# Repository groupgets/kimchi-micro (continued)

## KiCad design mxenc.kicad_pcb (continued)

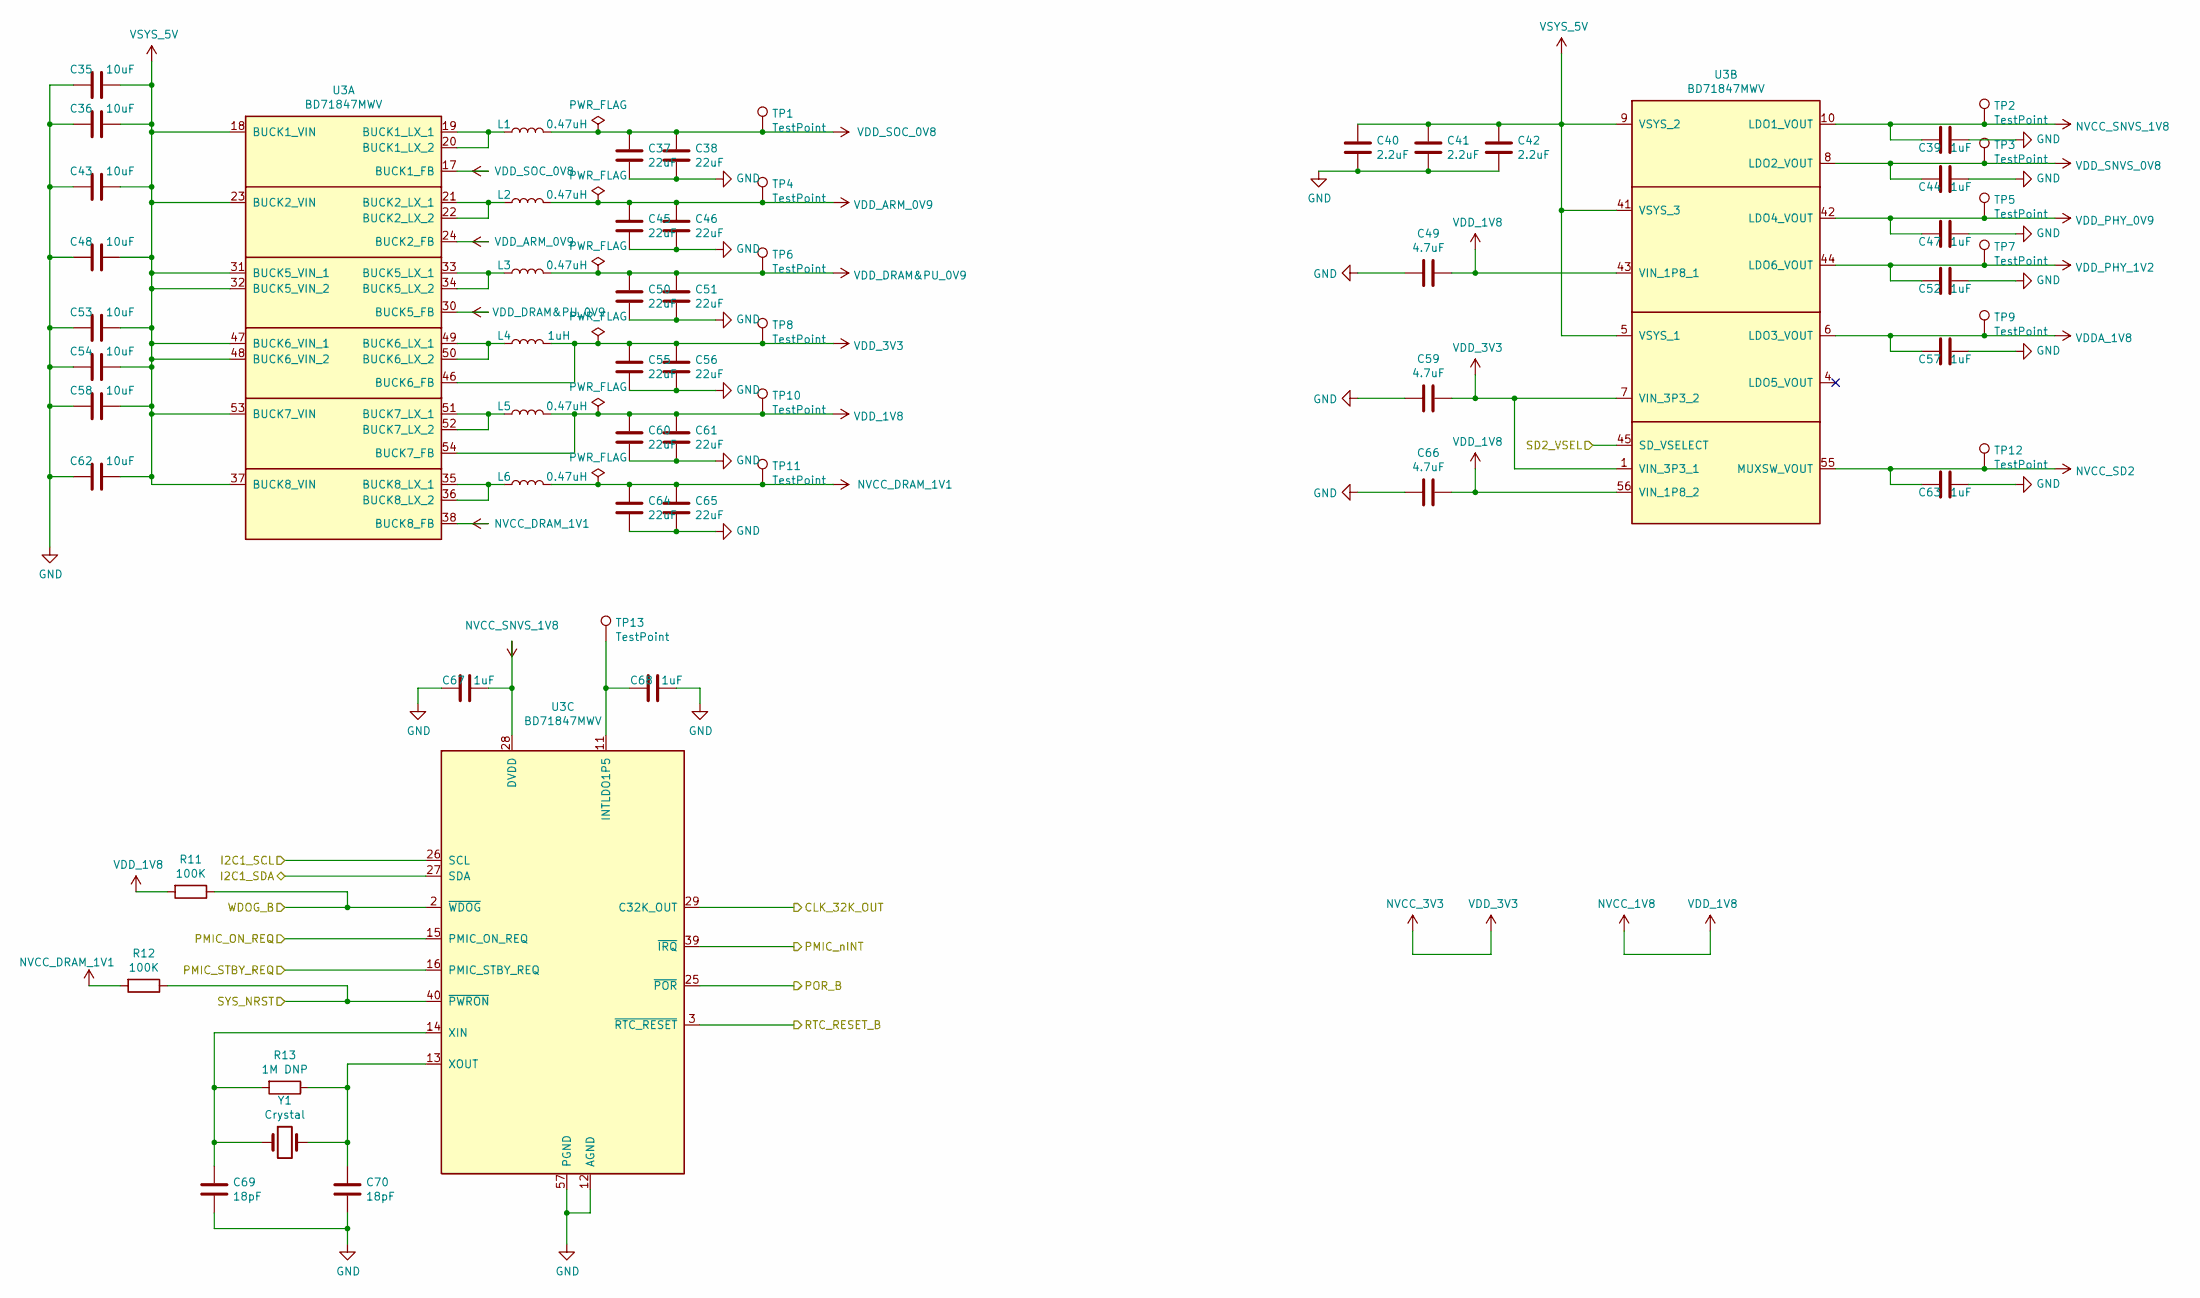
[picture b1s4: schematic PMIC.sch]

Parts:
C35, C36, C43, C48, C53, C54, C58, C62: 10uF; C_0603_1608Metric; Part CL10X106MO8NRNC
C37, C38, C45, C46, C50, C51, C55, C56, C60, C61, C64, C65: 22uF; C_0603_1608Metric; Part GRM188C80G226MEA0D
C39, C44, C47, C52, C57, C67, C68: 1uF; C_0402_1005Metric; Part GRM155C81A105KA12D
C40, C41, C42: 2.2uF; C_0402_1005Metric; Part GRM155C80J225ME95D
C49, C59, C66: 4.7uF; C_0402_1005Metric; Part GRM155C80J475MEAAD
C63: 1uF; C_0603_1608Metric; Part CL10B105MO8NNWC
C69, C70: 18pF; C_0402_1005Metric; Part GRM0335C1H180JA01D
L1, L2, L3, L5, L6: 0.47uH; L_0806; Part CIGT201610EHR47MNE
L4: 1uH; L_0806; Part CIGT201610EH1R0MNE
R11, R12: 100K; R_0402_1005Metric; Part RC0402JR-07100KL
R13: 1M DNP; R_0402_1005Metric
TP1, TP2, TP3, TP4, TP5, TP6, TP7, TP8, TP9, TP10, TP11, TP12, TP13: TestPoint; TestPoint_Pad_D1.0mm
U3: BD71847MWV; QFN-56_EP_7x7_Pitch0.4mm; Part BD71847AMWV-E2
Y1: Crystal; Crystal_SMD_3215-2Pin_3.2x1.5mm; Part ABS07-32.768KHZ-T

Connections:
/CLK_32K: U3.29 (C32K_OUT); also elsewhere on the board
/I2C1_SCL: U3.26 (SCL); also elsewhere on the board
/I2C1_SDA: U3.27 (SDA); also elsewhere on the board
/PMIC_ON_REQ: U3.15 (PMIC_ON_REQ); also elsewhere on the board
/PMIC_STBY_REQ: U3.16 (PMIC_STBY_REQ); also elsewhere on the board
/PMIC_nINT: U3.39 (~IRQ); also elsewhere on the board
/POR_B: U3.25 (~POR); also elsewhere on the board
/RTC_RESET_B: U3.3 (~RTC_RESET); also elsewhere on the board
/SD2_VSEL: U3.45 (SD_VSELECT); also elsewhere on the board
/SYS_NRST: R12.1, U3.40 (~PWRON)
/WDOG_B: R11.1, U3.2 (~WDOG); also elsewhere on the board
GND: C35.2, C36.2, C37.1, C38.1, C39.1, C40.2, C41.2, C42.2, C43.2, C44.1, C45.1, C46.1, C47.1, C48.2, C49.1, C50.1, C51.1, C52.1, C53.2, C54.2, C55.1, C56.1, C57.1, C58.2, C59.1, C60.1, C61.1, C62.2, C63.1, C64.1, C65.1, C66.1, C67.1, C68.2, C69.1, C70.1, U3.12 (AGND), U3.57 (PGND); also elsewhere on the board
NVCC_1V8: C49.2, C60.2, C61.2, C66.2, L5.2, R11.2, TP10.1, U3.43 (VIN_1P8_1), U3.54 (BUCK7_FB), U3.56 (VIN_1P8_2); also elsewhere on the board
NVCC_3V3: C55.2, C56.2, C59.2, L4.2, TP8.1, U3.1 (VIN_3P3_1), U3.7 (VIN_3P3_2), U3.46 (BUCK6_FB); also elsewhere on the board
NVCC_DRAM_1V1: C64.2, C65.2, L6.2, R12.2, TP11.1, U3.38 (BUCK8_FB); also elsewhere on the board
NVCC_SD2: C63.2, TP12.1, U3.55 (MUXSW_VOUT); also elsewhere on the board
NVCC_SNVS_1V8: C39.2, C67.2, TP2.1, U3.10 (LDO1_VOUT), U3.28 (DVDD); also elsewhere on the board
unnamed: C68.1, TP13.1, U3.11 (INTLDO1P5)
unnamed: C69.2, R13.2, U3.14 (XIN), Y1.1
unnamed: C70.2, R13.1, U3.13 (XOUT), Y1.2
unnamed: L1.1, U3.19 (BUCK1_LX_1), U3.20 (BUCK1_LX_2)
unnamed: L2.1, U3.21 (BUCK2_LX_1), U3.22 (BUCK2_LX_2)
unnamed: L3.1, U3.33 (BUCK5_LX_1), U3.34 (BUCK5_LX_2)
unnamed: L4.1, U3.49 (BUCK6_LX_1), U3.50 (BUCK6_LX_2)
unnamed: L5.1, U3.51 (BUCK7_LX_1), U3.52 (BUCK7_LX_2)
unnamed: L6.1, U3.35 (BUCK8_LX_1), U3.36 (BUCK8_LX_2)
VDDA_1V8: C57.2, TP9.1, U3.6 (LDO3_VOUT); also elsewhere on the board
VDD_ARM_0V9: C45.2, C46.2, L2.2, TP4.1, U3.24 (BUCK2_FB); also elsewhere on the board
VDD_DRAM&PU_0V9: C50.2, C51.2, L3.2, TP6.1, U3.30 (BUCK5_FB); also elsewhere on the board
VDD_PHY_0V9: C47.2, TP5.1, U3.42 (LDO4_VOUT); also elsewhere on the board
VDD_PHY_1V2: C52.2, TP7.1, U3.44 (LDO6_VOUT); also elsewhere on the board
VDD_SNVS_0V8: C44.2, TP3.1, U3.8 (LDO2_VOUT); also elsewhere on the board
VDD_SOC_0V8: C37.2, C38.2, L1.2, TP1.1, U3.17 (BUCK1_FB); also elsewhere on the board
VSYS_5V: C35.1, C36.1, C40.1, C41.1, C42.1, C43.1, C48.1, C53.1, C54.1, C58.1, C62.1, U3.5 (VSYS_1), U3.9 (VSYS_2), U3.18 (BUCK1_VIN), U3.23 (BUCK2_VIN), U3.31 (BUCK5_VIN_1), U3.32 (BUCK5_VIN_2), U3.37 (BUCK8_VIN), U3.41 (VSYS_3), U3.47 (BUCK6_VIN_1), U3.48 (BUCK6_VIN_2), U3.53 (BUCK7_VIN); also elsewhere on the board

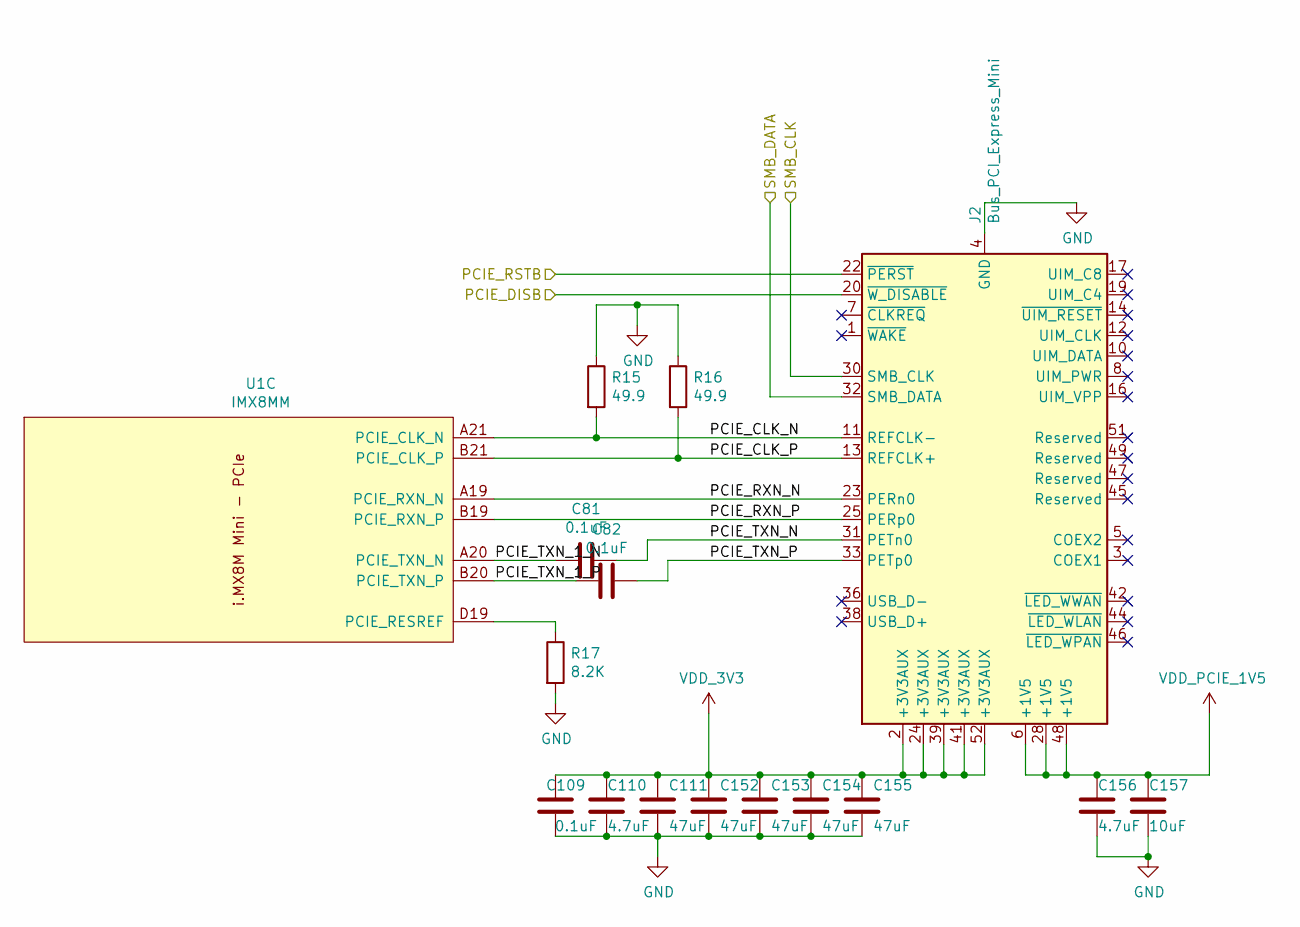
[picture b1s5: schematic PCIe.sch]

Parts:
C81, C82, C109: 0.1uF; C_0201_0603Metric; Part GRM033C80J104KE15D
C110, C156: 4.7uF; C_0402_1005Metric; Part GRM155C80J475MEAAD
C111, C152, C153, C154, C155: 47uF; C_0805_2012Metric; Part GRM21BC80G476ME15L
C157: 10uF; C_0402_1005Metric; Part GRM155C80J106ME11D
J2: Bus_PCI_Express_Mini; 1775838-2-NPTH; Part 1775838-2
R15, R16: 49.9; R_0201_0603Metric; Part RC0201FR-0749R9L
R17: 8.2K; R_0201_0603Metric; Part RC0201FR-078K2L
U1: IMX8MM; BGA-729_27x27_14.0x14.0mm; Part MIMX8MM6CVTKZAA

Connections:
/I2C3_SCL: J2.30 (SMB_CLK); also elsewhere on the board
/I2C3_SDA: J2.32 (SMB_DATA); also elsewhere on the board
/PCIE_DISB: J2.20 (~W_DISABLE); also elsewhere on the board
/PCIE_RSTB: J2.22 (~PERST); also elsewhere on the board
/PCIe/PCIE_CLK_N: J2.11 (REFCLK-), R15.2, U1.A21 (PCIE_CLK_N)
/PCIe/PCIE_CLK_P: J2.13 (REFCLK+), R16.2, U1.B21 (PCIE_CLK_P)
/PCIe/PCIE_RXN_N: J2.23 (PERn0), U1.A19 (PCIE_RXN_N)
/PCIe/PCIE_RXN_P: J2.25 (PERp0), U1.B19 (PCIE_RXN_P)
/PCIe/PCIE_TXN_1_N: C81.2, U1.A20 (PCIE_TXN_N)
/PCIe/PCIE_TXN_1_P: C82.2, U1.B20 (PCIE_TXN_P)
/PCIe/PCIE_TXN_N: C81.1, J2.31 (PETn0)
/PCIe/PCIE_TXN_P: C82.1, J2.33 (PETp0)
GND: C109.2, C110.2, C111.2, C152.2, C153.2, C154.2, C155.2, C156.2, C157.2, J2.4 (GND), J2.9 (GND), J2.15 (GND), J2.18 (GND), J2.21 (GND), J2.26 (GND), J2.27 (GND), J2.29 (GND), J2.34 (GND), J2.35 (GND), J2.37 (GND), J2.40 (GND), J2.43 (GND), J2.50 (GND), R15.1, R16.1, R17.2; also elsewhere on the board
NVCC_3V3: C109.1, C110.1, C111.1, C152.1, C153.1, C154.1, C155.1, J2.2 (+3V3AUX), J2.24 (+3V3AUX), J2.39 (+3V3AUX), J2.41 (+3V3AUX), J2.52 (+3V3AUX); also elsewhere on the board
unnamed: R17.1, U1.D19 (PCIE_RESREF)
VDD_PCIE_1V5: C156.1, C157.1, J2.6 (+1V5), J2.28 (+1V5), J2.48 (+1V5); also elsewhere on the board

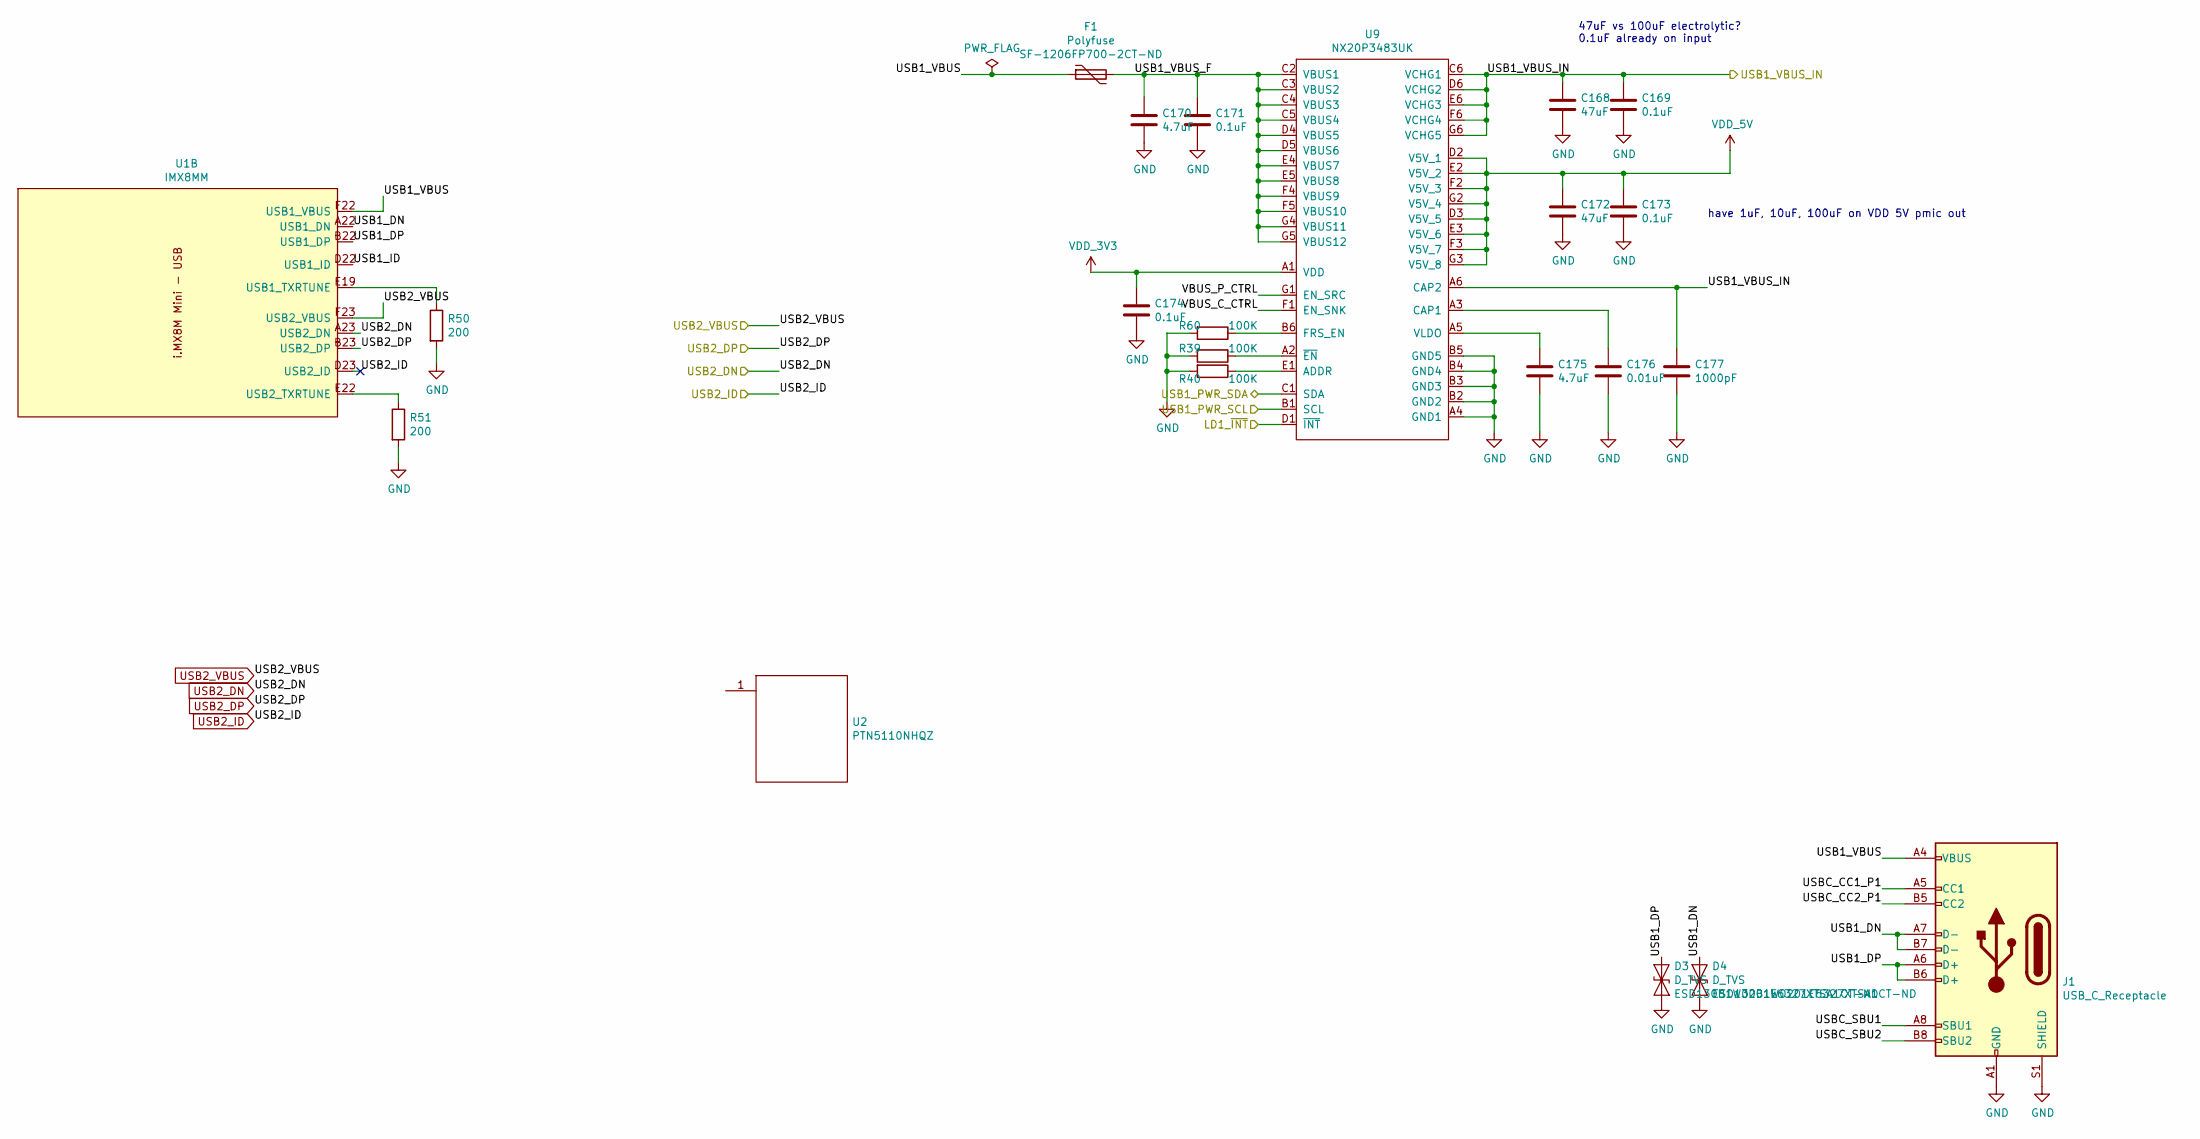
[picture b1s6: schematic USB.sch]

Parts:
C168, C172: 47uF; C_1210_3225Metric; Part GRM32EC81C476ME15L
C169, C171, C173, C174: 0.1uF; C_0402_1005Metric; Part GRM155R71E104KE14J
C170: 4.7uF; C_1210_3225Metric; Part CC1210MKX7R6BB475
C175: 4.7uF; C_0603_1608Metric; Part JMK107C6475MA-T
C176: 0.01uF; C_0201_0603Metric; Part GRM033R71C103KE14D
C177: 1000pF; C_0201_0603Metric; Part GRM033R71H102KA12J
D3, D4: D_TVS; D_0201_0603Metric; Part ESD130B1W0201E6327XTSA1
F1: Polyfuse; C_1206_3216Metric; Part SF-1206FP700-2
J1: USB_C_Receptacle; GCT_USB4110-GF-A; Part DX07S024JJ2R1300
R39, R40, R60: 100K; R_0201_0603Metric; Part RC0201JR-07100KL
R50, R51: 200; R_0201_0603Metric; Part RC0201FR-07200RL
U1: IMX8MM; BGA-729_27x27_14.0x14.0mm; Part MIMX8MM6CVTKZAA
U2: PTN5110NHQZ; HX2QFN-16_EP_2.85x2.85_Pitch0.4mm
U9: NX20P3483UK; BGA-42_6x7_2.51x2.91mm; Part NX20P3483UK

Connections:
/I2C3_SCL: U9.B1 (SCL); also elsewhere on the board
/I2C3_SDA: U9.C1 (SDA); also elsewhere on the board
/LD1_~INT: U9.D1 (~INT); also elsewhere on the board
/USB/USB1_DN: D4.1 (A1), J1.A7 (D-), J1.B7 (D-), U1.A22 (USB1_DN)
/USB/USB1_DP: D3.1 (A1), J1.A6 (D+), J1.B6 (D+), U1.B22 (USB1_DP)
/USB/USB1_VBUS: F1.1, J1.A4 (VBUS), J1.A9 (VBUS), J1.B4 (VBUS), J1.B9 (VBUS), U1.F22 (USB1_VBUS)
/USB/USB1_VBUS_F: C170.1, C171.1, F1.2, U9.C2 (VBUS1), U9.C3 (VBUS2), U9.C4 (VBUS3), U9.C5 (VBUS4), U9.D4 (VBUS5), U9.D5 (VBUS6), U9.E4 (VBUS7), U9.E5 (VBUS8), U9.F4 (VBUS9), U9.F5 (VBUS10), U9.G4 (VBUS11), U9.G5 (VBUS12)
/VBUS_IN: C168.1, C169.1, C177.1, U9.A6 (CAP2), U9.C6 (VCHG1), U9.D6 (VCHG2), U9.E6 (VCHG3), U9.F6 (VCHG4), U9.G6 (VCHG5); also elsewhere on the board
GND: C168.2, C169.2, C170.2, C171.2, C172.2, C173.2, C174.2, C175.2, C176.2, C177.2, D3.2 (A2), D4.2 (A2), J1.A1 (GND), J1.A12 (GND), J1.B1 (GND), J1.B12 (GND), J1.S1 (SHIELD), R39.2, R40.2, R50.2, R51.2, R60.2, U9.A4 (GND1), U9.B2 (GND2), U9.B3 (GND3), U9.B4 (GND4), U9.B5 (GND5); also elsewhere on the board
NVCC_3V3: C174.1, U9.A1 (VDD); also elsewhere on the board
unnamed: C175.1, U9.A5 (VLDO)
unnamed: C176.1, U9.A3 (CAP1)
unnamed: R39.1, U9.A2 (~EN)
unnamed: R40.1, U9.E1 (ADDR)
unnamed: R50.1, U1.E19 (USB1_TXRTUNE)
unnamed: R51.1, U1.E22 (USB2_TXRTUNE)
unnamed: R60.1, U9.B6 (FRS_EN)
USB2_DN: U1.A23 (USB2_DN); also elsewhere on the board
USB2_DP: U1.B23 (USB2_DP); also elsewhere on the board
USB2_ID: U1.D23 (USB2_ID); also elsewhere on the board
USB2_VBUS: U1.F23 (USB2_VBUS); also elsewhere on the board
VDD_5V: C172.1, C173.1, U9.D2 (V5V_1), U9.D3 (V5V_5), U9.E2 (V5V_2), U9.E3 (V5V_6), U9.F2 (V5V_3), U9.F3 (V5V_7), U9.G2 (V5V_4), U9.G3 (V5V_8); also elsewhere on the board

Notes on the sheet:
47uF vs 100uF electrolytic? 0.1uF already on input
have 1uF, 10uF, 100uF on VDD 5V pmic out

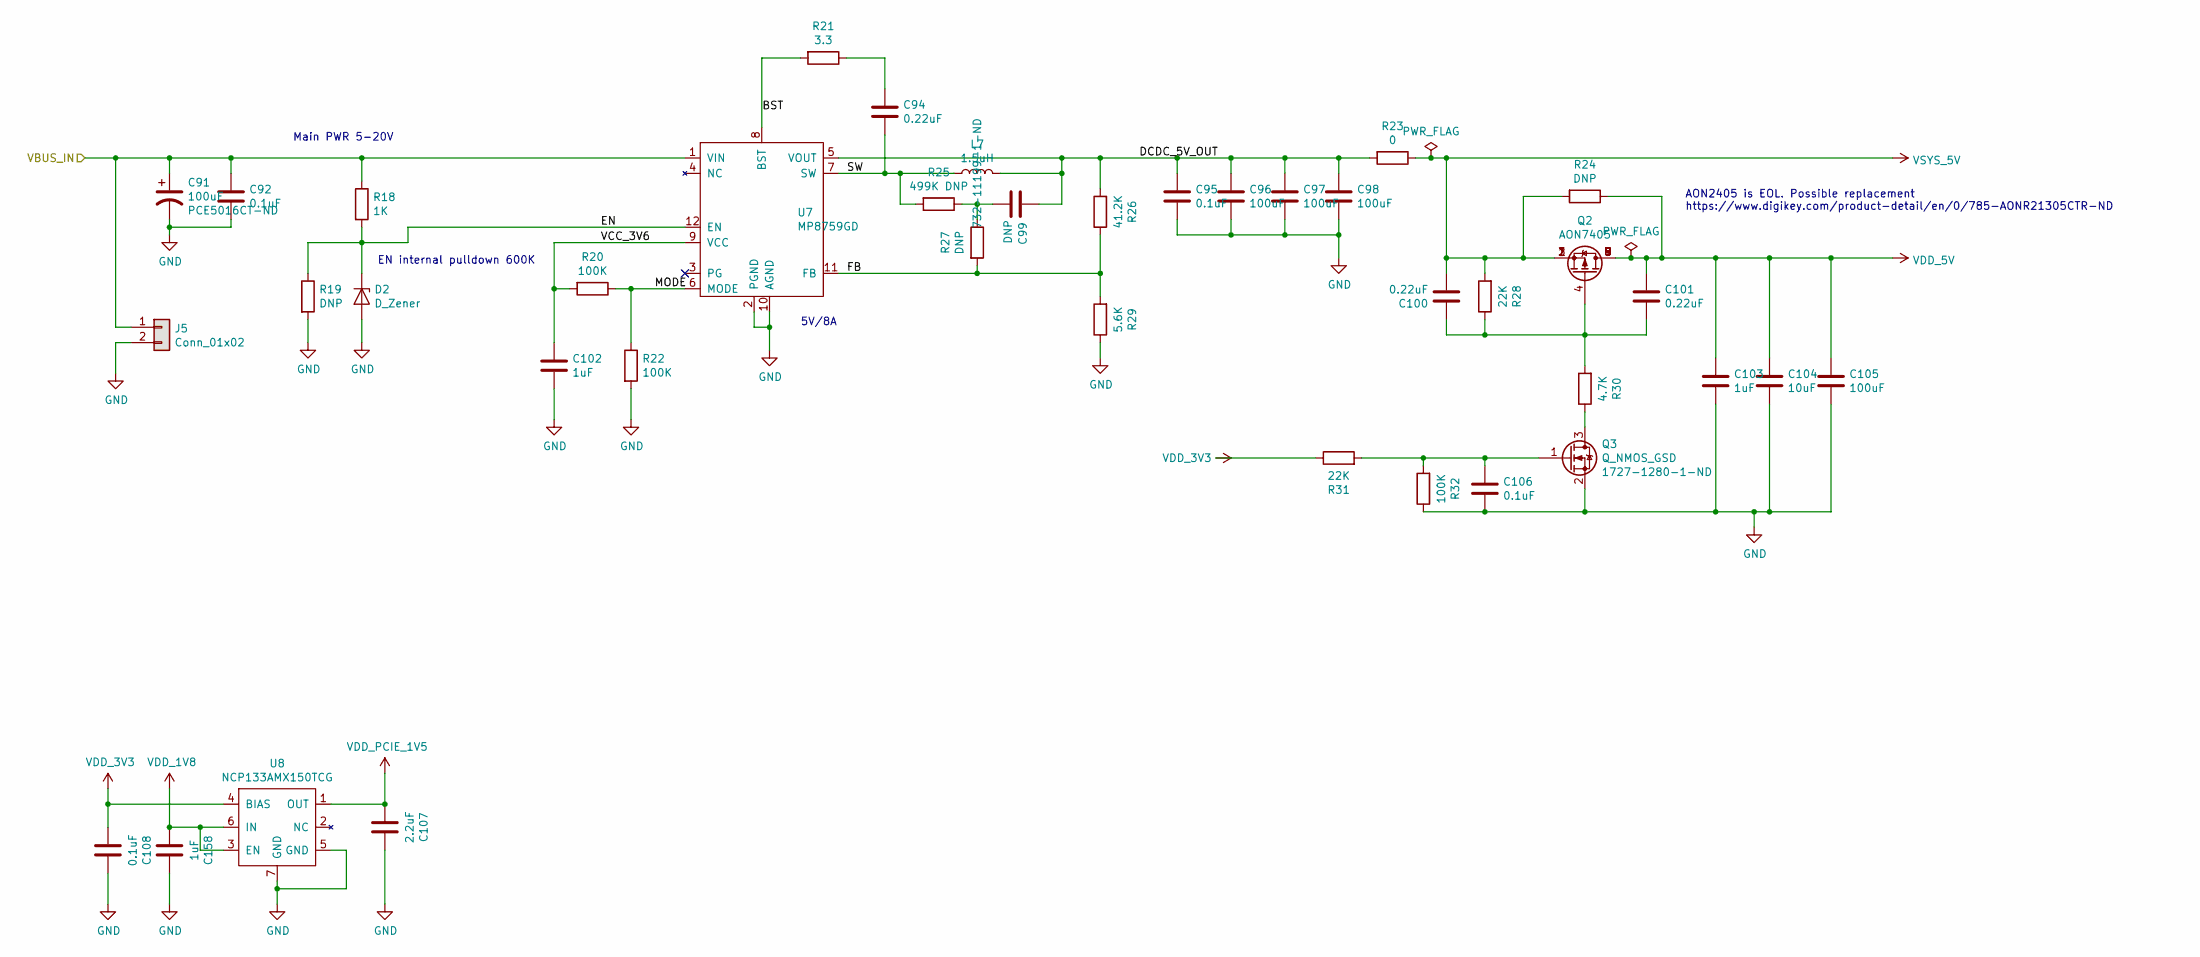
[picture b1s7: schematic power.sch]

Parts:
C91: 100uF; C_Elec_6.3x5.8; Part EEE-FT1V101AP
C92, C95, C106: 0.1uF; C_0402_1005Metric; Part GRM155R71E104KE14J
C94, C100, C101: 0.22uF; C_0402_1005Metric; Part GRM155C8YA224ME01D
C96, C97, C98, C105: 100uF; C_1210_3225Metric; Part GRM32EC70J107ME15L
C99: DNP; C_0402_1005Metric
C102, C103, C158: 1uF; C_0402_1005Metric; Part GRM155C81A105KA12D
C104: 10uF; C_0805_2012Metric_Pad1.15x1.40mm_HandSolder; Part CL21X106KPYNNNE
C107: 2.2uF; C_0402_1005Metric; Part GRM155C80J225ME95D
C108: 0.1uF; C_0201_0603Metric; Part GRM033C80J104KE15D
D2: D_Zener; D_SOD-323; Part MM3Z4V3ST1G
J5: Conn_01x02; JST_XH_B2B-XH-A_1x02_P2.50mm_Vertical; Part SM02B-GHS-TB(LF)(SN)
L7: 1.5uH; L_Wuerth_MAPI-4020; Part 74438357015
Q2: AON7405; DFN-8-1EP_3x3mm_P0.65mm_EP1.7x2.05mm; Part AON7405
Q3: Q_NMOS_GSD; SOT-323_SC-70; Part NX3008NBKW,115
R18: 1K; R_0402_1005Metric; Part RC0402JR-071KL
R19, R24, R27: DNP; R_0402_1005Metric
R20, R22, R32: 100K; R_0402_1005Metric; Part RC0402JR-07100KL
R21: 3.3; R_0603_1608Metric; Part MCT06030C3308FP500
R23: 0; R_0805_2012Metric; Part CRCW08050000Z0EAHP
R25: 499K DNP; R_0402_1005Metric
R26: 41.2K; R_0402_1005Metric; Part ERJ-2RKF4122X
R28, R31: 22K; R_0402_1005Metric; Part ERJ-2GEJ223X
R29: 5.6K; R_0402_1005Metric; Part ERJ-2RKF5601X
R30: 4.7K; R_0402_1005Metric; Part ERJ-2RKF4701X
U7: MP8759GD; QFN-16_2x3_Pitch0.5mm; Part MP8759GD-Z
U8: NCP133AMX150TCG; XDFN6_1.20x1.20_0.40P; Part NCP133AMX150TCG

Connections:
/Power/BST: R21.2, U7.8 (BST)
/Power/DCDC_5V_OUT: C95.1, C96.1, C97.1, C98.1, C99.1, L7.2, R23.2, R26.2, U7.5 (VOUT)
/Power/EN: D2.1 (K), R18.2, R19.1, U7.12 (EN)
/Power/FB: R26.1, R27.2, R29.2, U7.11 (FB)
/Power/MODE: R20.1, R22.1, U7.6 (MODE)
/Power/SW: C94.2, L7.1, R25.2, U7.7 (SW)
/Power/VCC_3V6: C102.1, R20.2, U7.9 (VCC)
/VBUS_IN: C91.1, C92.1, J5.1, R18.1, U7.1 (VIN); also elsewhere on the board
GND: C91.2, C92.2, C95.2, C96.2, C97.2, C98.2, C102.2, C103.2, C104.2, C105.2, C106.2, C107.1, C108.1, C158.1, D2.2 (A), J5.2, Q3.2 (S), R19.2, R22.2, R29.1, R32.1, U7.2 (PGND), U7.10 (AGND), U8.5 (GND), U8.7 (GND); also elsewhere on the board
NVCC_1V8: C158.2, U8.3 (EN), U8.6 (IN); also elsewhere on the board
NVCC_3V3: C108.2, R31.1, U8.4 (BIAS); also elsewhere on the board
unnamed: C94.1, R21.1
unnamed: C99.2, R25.1, R27.1
unnamed: C100.1, C101.2, Q2.4 (G), R28.1, R30.2
unnamed: C106.1, Q3.1 (G), R31.2, R32.2
unnamed: Q3.3 (D), R30.1
VDD_5V: C101.1, C103.1, C104.1, C105.1, Q2.5 (D), Q2.6 (D), Q2.7 (D), Q2.8 (D), Q2.9 (D), R24.1; also elsewhere on the board
VDD_PCIE_1V5: C107.2, U8.1 (OUT); also elsewhere on the board
VSYS_5V: C100.2, Q2.1 (S), Q2.2 (S), Q2.3 (S), R23.1, R24.2, R28.2; also elsewhere on the board

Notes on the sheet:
5V/8A
Main PWR 5-20V
EN internal pulldown 600K
AON2405 is EOL. Possible replacement https://www.digikey.com/product-detail/en/0/785-AONR21305CTR-ND

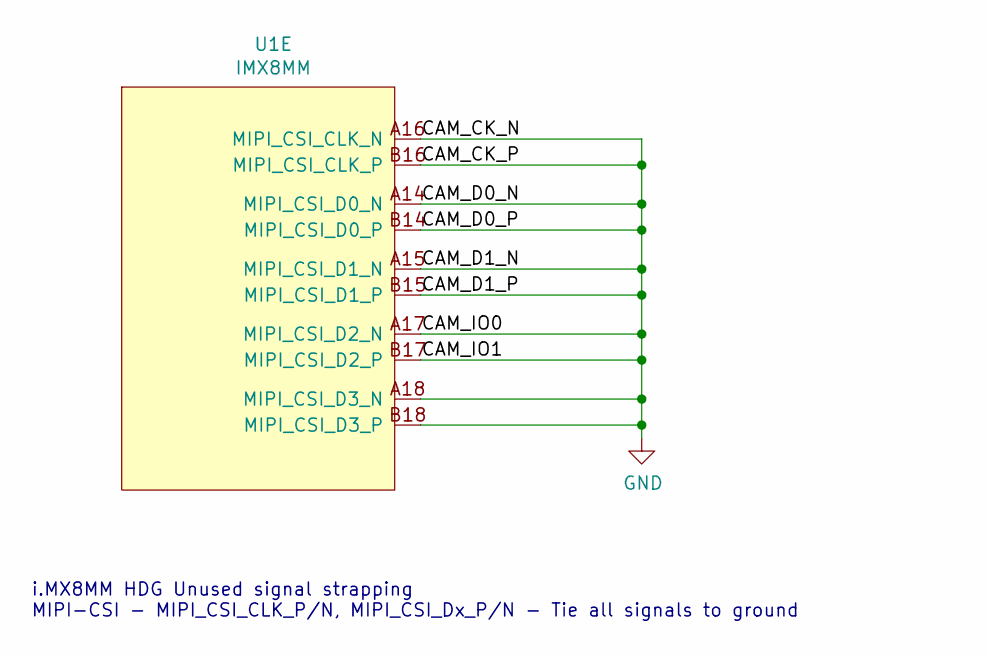
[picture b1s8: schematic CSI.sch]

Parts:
U1: IMX8MM; BGA-729_27x27_14.0x14.0mm; Part MIMX8MM6CVTKZAA

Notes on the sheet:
i.MX8MM HDG Unused signal strapping MIPI-CSI - MIPI_CSI_CLK_P/N, MIPI_CSI_Dx_P/N - Tie all signals to ground

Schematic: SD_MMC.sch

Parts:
C71: 4.7uF; C_0402_1005Metric; Part GRM155C80J475MEAAD
C72, C73, C74, C75, C76, C80: 0.22uF; C_0201_0603Metric; Part GRM033C80J224KE90D
C77: 10uF; C_0402_1005Metric; Part GRM155C80J106ME11D
C78: 0.22uF; C_0402_1005Metric; Part GRM155C8YA224ME01D
C79: 1uF; C_0402_1005Metric; Part GRM155C81A105KA12D
J3: Micro_SD_Card; 114-00841-68; Part 114-00841-68
R14: 10K; R_0402_1005Metric; Part ERJ-2GEJ103X
U1: IMX8MM; BGA-729_27x27_14.0x14.0mm; Part MIMX8MM6CVTKZAA
U5: SDINBDG4-8G; BGA153C50P14X14_1300X1150X80N; Part SDINBDG4-8G-I1

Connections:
/SD/MMC/EMMC_CLK: U1.V26 (SD1_CLK), U5.M6 (CLK)
/SD/MMC/EMMC_CMD: U1.V27 (SD1_CMD), U5.M5 (CMD)
/SD/MMC/EMMC_DAT0: U1.Y27 (SD1_DATA0), U5.A3 (DAT0)
/SD/MMC/EMMC_DAT1: U1.Y26 (SD1_DATA1), U5.A4 (DAT1)
/SD/MMC/EMMC_DAT2: U1.T27 (SD1_DATA2), U5.A5 (DAT2)
/SD/MMC/EMMC_DAT3: U1.T26 (SD1_DATA3), U5.B2 (DAT3)
/SD/MMC/EMMC_DAT4: U1.U27 (SD1_DATA4), U5.B3 (DAT4)
/SD/MMC/EMMC_DAT5: U1.U26 (SD1_DATA5), U5.B4 (DAT5)
/SD/MMC/EMMC_DAT6: U1.W27 (SD1_DATA6), U5.B5 (DAT6)
/SD/MMC/EMMC_DAT7: U1.W26 (SD1_DATA7), U5.B6 (DAT7)
/SD/MMC/EMMC_RCLK: U1.R24 (SD1_STROBE), U5.H5 (RCLK)
/SD/MMC/EMMC_RST: U1.R23 (NAND_DQS/GPIO3[14]), U5.K5 (RST_N)
/SD/MMC/EMMC_VDDI: C79.1, C80.1, U5.C2 (VDDI)
/SD/MMC/SD_CD: J3.10 (DET_A), R14.1, U1.AA26 (SD2_CD_B)
/SD/MMC/SD_CLK: J3.5 (CLK), U1.W23 (SD2_CLK)
/SD/MMC/SD_CMD: J3.3 (CMD), U1.W24 (SD2_CMD)
/SD/MMC/SD_DAT0: J3.7 (DAT0), U1.AB23 (SD2_DATA0)
/SD/MMC/SD_DAT1: J3.8 (DAT1), U1.AB24 (SD2_DATA1)
/SD/MMC/SD_DAT2: J3.1 (DAT2), U1.V24 (SD2_DATA2)
/SD/MMC/SD_DAT3: J3.2 (DAT3/CD), U1.V23 (SD2_DATA3)
GND: C71.2, C72.2, C73.2, C74.2, C75.2, C76.2, C77.2, C78.2, C79.2, C80.2, J3.6 (VSS), J3.9 (DET_B), J3.11 (SHIELD), U5.A6 (VSS_A6), U5.C4 (VSSQ_C4), U5.E7 (VSS_E7), U5.G5 (VSS_G5), U5.H10 (VSS_H10), U5.J5 (VSS_J5), U5.K8 (VSS_K8), U5.N2 (VSSQ_N2), U5.N5 (VSSQ_N5), U5.P4 (VSSQ_P4), U5.P6 (VSSQ_P6); also elsewhere on the board
NVCC_1V8: C74.1, C75.1, C76.1, C77.1, U5.C6 (VCCQ_C6), U5.M4 (VCCQ_M4), U5.N4 (VCCQ_N4), U5.P3 (VCCQ_P3), U5.P5 (VCCQ_P5); also elsewhere on the board
NVCC_3V3: C71.1, C72.1, C73.1, U5.E6 (VCC_E6), U5.F5 (VCC_F5), U5.J10 (VCC_J10), U5.K9 (VCC_K9); also elsewhere on the board
NVCC_SD2: C78.1, J3.4 (VDD), R14.2; also elsewhere on the board

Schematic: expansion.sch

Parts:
J7, J9: DF40HC(3.5)-60DS; DF40C-60DP
U1: IMX8MM; BGA-729_27x27_14.0x14.0mm; Part MIMX8MM6CVTKZAA

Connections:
/Expansion/DISP_CK_N: J9.35, U1.A11 (MIPI_DSI_CLK_N)
/Expansion/DISP_CK_P: J9.36, U1.B11 (MIPI_DSI_CLK_P)
/Expansion/DISP_D0_N: J9.31, U1.A9 (MIPI_DSI_D0_N)
/Expansion/DISP_D0_P: J9.32, U1.B9 (MIPI_DSI_D0_P)
/Expansion/DISP_D1_N: J9.33, U1.A10 (MIPI_DSI_D1_N)
/Expansion/DISP_D1_P: J9.34, U1.B10 (MIPI_DSI_D1_P)
/Expansion/DISP_D2_N: J9.37, U1.A12 (MIPI_DSI_D2_N)
/Expansion/DISP_D2_P: J9.38, U1.B12 (MIPI_DSI_D2_P)
/Expansion/DISP_D3_N: J9.39, U1.A13 (MIPI_DSI_D3_N)
/Expansion/DISP_D3_P: J9.40, U1.B13 (MIPI_DSI_D3_P)
/SD/MMC/EMMC_RST: U1.R23 (NAND_DQS/GPIO3[14]); also elsewhere on the board
GND: J7.MP, J9.MP; also elsewhere on the board
GPIO3[5]: U1.K27 (NAND_CLE/GPIO3[5]); also elsewhere on the board
GPIO3[12]: U1.K26 (NAND_DATA6/GPIO3[12]); also elsewhere on the board
JTAG_MOD: J9.51; also elsewhere on the board
JTAG_TCK: J9.56; also elsewhere on the board
JTAG_TDI: J9.54; also elsewhere on the board
JTAG_TDO: J9.53; also elsewhere on the board
JTAG_TMS: J9.55; also elsewhere on the board
JTAG_TRST_B: J9.52; also elsewhere on the board
USB2_DN: J9.59; also elsewhere on the board
USB2_DP: J9.60; also elsewhere on the board
USB2_ID: J9.58; also elsewhere on the board
USB2_VBUS: J9.57; also elsewhere on the board

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
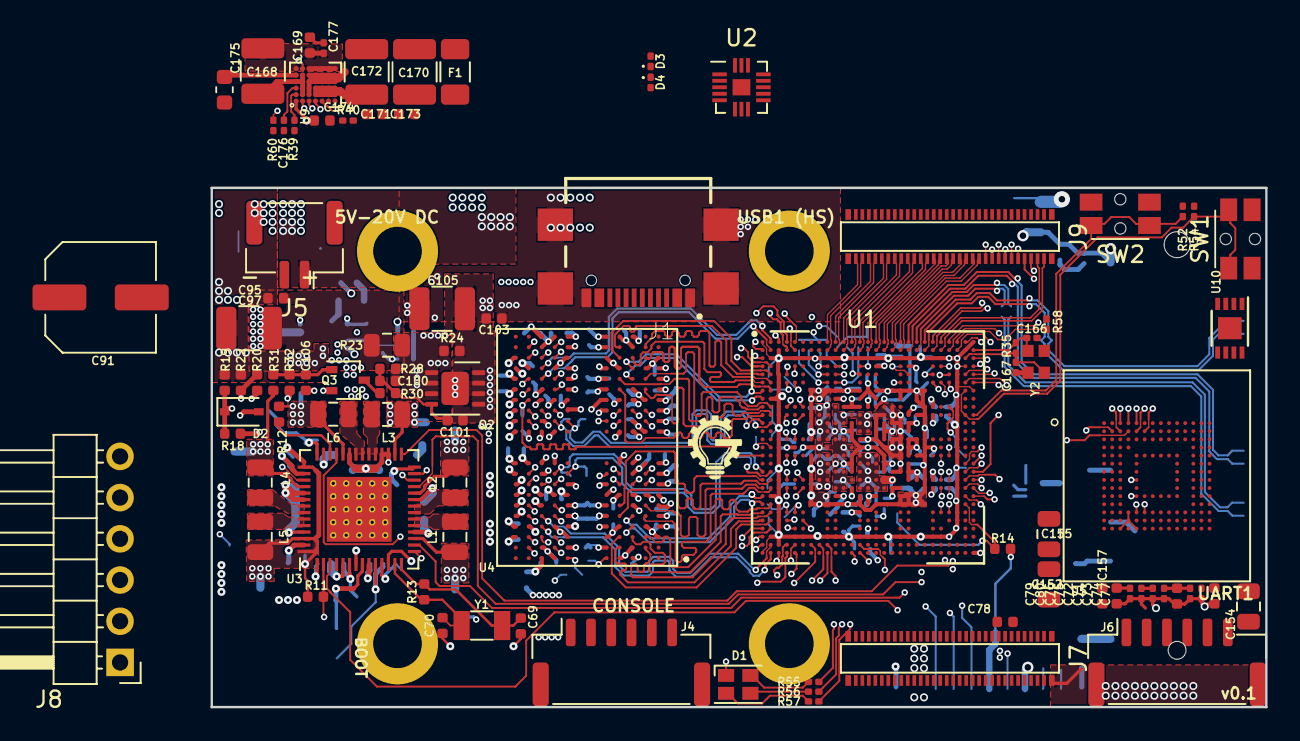
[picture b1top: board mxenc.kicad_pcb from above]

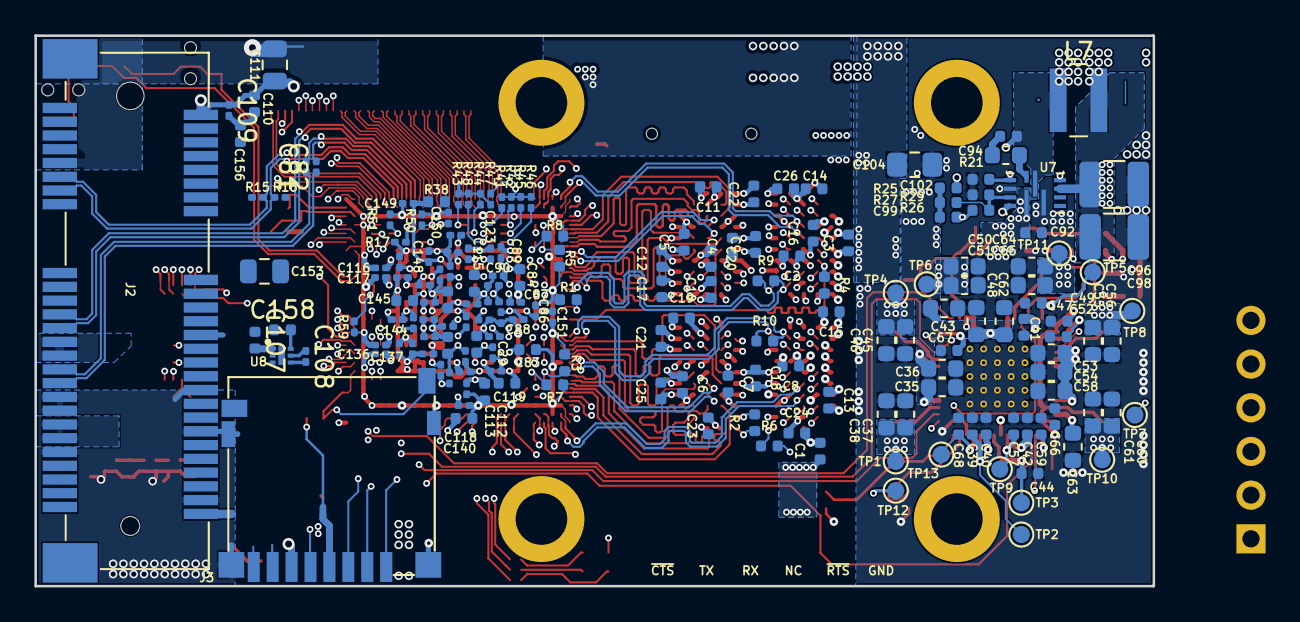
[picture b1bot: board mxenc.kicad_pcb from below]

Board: 8 copper layers, 65.0 x 32.0 mm, 273 parts (181 on the bottom side), 222 nets.

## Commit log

2020-03-20 stitch ground a little better around pcie
2020-03-20 give emmc a more solid connection to power and ground
2020-03-20 Improve bypass capacitor placement around dram and processor
2020-03-20 isolated vout a bit more from sw on power input, and better vin connection
2020-03-20 Add license CERN-OHL-S
2020-03-20 improved 5v power supply routing
2020-03-20 re-layout power input switcher
2020-03-20 reroute power input again, move switcher to back side
2020-03-20 Add zener instead of fet to limit voltage on power input EN
2020-03-20 Add esd protection for usb
2020-03-20 Plot gerbers for v0.1 board
2020-03-20 Tie boot0 to btn0 / sw1
2020-03-20 Tweak trace widths to reflect stackup for first run
2020-03-20 Improve routing for major arm supplies
2020-03-20 Add logo board name and version to silk
2020-03-20 Remove reference to SDINBDG4-8G.lib which isn't used
2020-03-20 Improve ground returns for ls and hs imx clocks, improve decoupling for usb-c mux
2020-03-20 Re-add gg logo
2020-03-20 Fix link to local footprint library
2020-03-20 Complete entry of bom
2020-03-20 add stencil jig sources
2020-03-20 rerouted sd, added some gpio, started power input
2020-03-20 rough layout, routing for emmc and csi, dsi, pcie
2020-03-20 More new layout, buttons, and routing
2020-03-20 Cleaned up fab drawings and centered entire layout on page
2020-03-20 wip more new layout
2020-03-20 UIM and USB routing for PCIE to expansion
2020-03-20 add sai, mdio, sdhc to headers
2020-03-20 Ground mounting pads and route ecspi to expansion
2020-03-20 Finish remaining routing
2020-03-20 wip more uart routing
2020-03-20 prior to rerouting sai lanes
2020-03-20 Add esd protection to cc lines
2020-03-20 Fix up main power supply decoupling
2020-03-20 Change expansion audio routing to sai2/3
2020-03-20 Additional capacitance for PCIe to support high power modules
2020-03-20 Set up for battery NTC and add a power button
2020-03-20 Switch 5V buck for 1S battery charger boost
2020-03-20 Change power input to JST-PH
2020-03-20 Slightly better ground coupling around charger
2020-03-20 Added PicoSPOX battery connection option w/ NTC
2020-03-20 Cleanup remaining DRC problems from schematic
2020-03-20 Re-annotate schematics, add dnp field, and silkscreen cleanup
2020-03-20 Add header for main power input
2020-03-20 Added zener for tvs on pcie
2020-03-20 Fixed a few comments related to component reference and make sure we're displaying dnp
2020-03-20 Split mounting holes from pcie and put them on the front side
2020-03-20 Add 3D models for MP2636 and NX20P3483UK, clean up others
2020-03-20 Spaced caps on pmic out a bit more
2020-03-20 Simplify control of VDD_5V with load switch
2020-03-20 Better passive routing around power supplies
2020-03-20 Add license to back silk
2020-03-20 Add license information to schematics
2020-03-20 Update project name to kimchi_micro
2020-03-20 Add project readme
2020-03-20 Fix a few capacitor footprints marked as resistors
2020-03-20 Update front stencil so not break off pins
2020-03-20 Corrections for bom of v0.1
2020-03-21 Move sbc design files to subdirectory
2020-03-21 Created github pages docs
2020-03-21 add images
2020-03-21 Add ulid expansion module kicad template submodule
2020-03-21 Add board image to readme
2020-03-22 Clean up bom and add config for KiBoM
2020-03-22 Add stackup information
2020-03-30 Add battery monitor and protection circuit
2020-04-09 Add production files for v0.9
2020-04-09 0.9 update
2020-04-09 Update submodule for kicad template compatibility
2020-04-28 Updated board renders
2020-04-28 4/27 update
2020-04-28 fix image links
2020-04-28 Update front page
2020-04-28 Fix front page typos
2020-06-05 BOM and misc fixes for production of 0.9 boards
2020-06-11 Don't stuff C125-127
    These 3x 220uF caps are pulling down the 3v3 at boot. We need a
    load switch in the next rev.
2020-08-11 Supply microsd with vdd_3v3 instead of nvcc_sd2
    Fixes #2
2020-08-11 Correct swapped sda/scl on U9
    Fixes #4
2020-08-11 Correct U12 BIN pin connection
    Fixes #5
2020-08-13 Add load switch and separate power for VDD_PCIE_3V3
    Fixes #3
2020-08-13 DNP PCIE_3V3_EN pull-down
    This part has an internal 2M pulldown, so this is no needed, but
    could be useful for rework (if we want to use a different signal
    to turn this on, for example). Move things around a bit to make this
    possible.
2020-08-20 Update BoM and add some errata notes for v0.9 builds moving forward
2020-08-20 Add update for v0.9 assembly
2020-08-20 Change to just-the-docs theme
2020-08-20 Move updates to side panel
2020-08-20 Add aux links to config
2020-08-20 Try to fix updates nav
2020-08-20 Add license in footer
2020-08-20 Add hardware assembly notes
2020-08-20 Add start of software documentation
2020-08-20 Add fusing description
2020-08-20 Update front stencil fixture for 6.8 mm mPCIE
2020-08-20 Change mPCIe connector to taller 2041262-1
    Fixes #7
2020-08-20 Add expansion section
2020-08-20 Add specifications to about
2020-08-20 assembly: add link to rework/errata
2020-08-20 software: yocto: fix distro selection
2020-09-04 Add low-side FET to properly disconnect battery on fault
    What was done in v0.9 to disable charge/discharge by driving IO on
    the charger circuit didn't really work out. Further, it had no way
    of monitoring overcurrent during discharge.
    Add a FED on the low side of the pack that can be controlled by the
    protection circuit, since this is how it is supposed to work.
    Fixes #6
2020-09-04 Measure battery voltage for monitor at same place as charger
    There was a small offset between the two, so this is just a small
    optimization to keep them as close as possible.
2020-09-04 Bring charger inductor in from edge just a little
2020-09-04 Enable charging by default, remove processor control
    Having the charge enable hooked up to the processor was problematic
    when the pin is not configured. There's not a great case for needing
    to have the processor enable/disable charging, so just leave it
    enabled.
2020-09-28 Fill in missing part numbers for bom
2020-09-28 Production files for v0.91
2021-02-21 Replace system and charger LEDs with smaller 0404 RGB LED
2021-02-22 Move power button side of board with USB
2021-02-22 Remove standoffs from board and update 3d model
2021-03-20 Add vbus to expansion connector and bugfix for battery cutoff
    This will allow lids to supply power to charge the battery.
    The battery cutoff circuit needs V- connected to pack ground, so
    this was also fixed.
2021-03-20 Change common 22uF part from 4V to 6.3V
    Most placements don't require 5V, but a few do. The 4V part is no
    longer stocking as well, and price is similar, so change all to
    6.3V version.
2021-03-20 Remove boost feedback resistor R42
    This part was added in error, take it out
2021-03-20 Fixes for battery cutoff circuit (again)
    The DOUT side is supposed to be connected to the battery, and COUT
    to the board facing side. This is now correct.
2021-06-22 Reduced numerous 3d model sizes and fixups for KiCadStepUp
    No changes to board
2021-06-23 Production output for 0.92 and updated lid template
2021-06-26 Update lid submodule to v0.92 version
2021-07-28 Update lids list
2021-07-28 Add pre-production sale update
2021-07-28 Update expansion diagram
2021-07-28 Update images
2021-07-28 expansion: add csi camera lid
2024-06-06 Create CNAME
2024-06-06 Update configuration for new subdomain
2024-06-06 readme: Update image URL
    Different pages subdomain while there are issue with labs.
2024-06-06 Update CNAME
2024-11-16 Updating to KiCAD 8 and part number updates
    ## Schematic
    Part number updates
    - R41 changed from "RC0201FR-0778R7L" to "RMCF0201FT78K7"
    - R71, R72 changed from "RC0201JR-071ML" to "RC0201JR-075M1L"
    - U10, U13 alternate PN "NCP339BFCT2G" added
    ## PCB
2024-11-21 Moved buttons to allow for v-score panel
    R2 and R3 pulldown resistors moved to make space.
    U13 and J3 nudged as well.
2024-11-22 Updated production files and fixed schematic link issue.
    Fixed schematic unit number issue and re-linked to PCB.
    New gerbers, STEP file, schematic PDF.
    Deleted old KiCAD 6 files.
2024-12-06 Updating board settings
    Reduced solder mask expansion to 1 mil and minimum web width to 6 mil.
2024-12-19 Updated production files
    Exported new production files, updated rev number and dates on schematic and PCB.
2024-12-28 Moved pwr silkscreen label
    pwr label was still at the old button location. Moved it across to the new location. Updated front silkscreen gerber layer.
2025-10-10 assembly.md: fix image links
2025-10-10 expansion.md: fix image links
2025-10-10 programming.md: fix image links
